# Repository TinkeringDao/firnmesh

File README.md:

# firnmesh

Sub-zero solar Li-Ion MPPT power management, `< 1 µA` QSPI sleep, C++17 host seam tests, and a zero-dependency USB serial/DFU utility (`p1_tool.py`) for **Seeed SenseCAP Solar Node P1-Pro** running as an unattended [MeshCore](https://github.com/meshcore-dev/MeshCore) LoRa repeater through continental winter frost (`-15 °C` nights and multi-week stratus fog).

Target hardware profile: `XIAO nRF52840 Plus` + `Wio-SX1262` (`+22 dBm`) + `XIAO L76K GNSS` + `P25Q16H` 2 MB QSPI flash + `CN3165` solar MPPT charger + `3350 mAh` 18650 NMC cell, tested on a rooftop mast with a `6.5 dBi` 868 MHz fiberglass omnidirectional antenna.

## What Stock `SenseCap_Solar_repeater` (`v1.18.0`) Gets Wrong on Hardware

Inspecting the stock `v1.18.0-81dbae5` UF2 binary and measuring live rail currents turned up several board-level bugs that drain a solar repeater in winter:

1. `SenseCapSolarBoard` inherited `NRF52Board` (LDO regulator) instead of `NRF52BoardDCDC`, omitted `-D NRF52_POWER_MANAGEMENT=1` (`0` `NRF_LPCOMP` references in the binary), left `NRF_WDT` disabled, and spun the CPU with `powersaving_enabled=0` (`3.6 mA` idle).
2. Unpowered `XIAO L76K` GNSS drew `1.8 mA` (`~43 mAh/day`) continuously via ESD protection diodes because `UART1 TX` (`P1.11`) stayed driven at `3.3 V` when `GPS_EN` went low, and calling `_location->stop()` before `Serial1.end()` wedged `NRF_UARTE0` on a `0 V` RX break condition (`S4-F7`).
3. The onboard `P25Q16H` 2 MB QSPI flash was never placed into Deep Power-Down (`0xB9`), while `PINS_COUNT=21` blocked `D21..D26`. Using the hardware `NRF_QSPI` peripheral triggers nRF52840 Errata 122 (`+1.2 mA` leak), so this port bit-bangs SPI Mode 0 `0xAB` + `0xB9` and disconnects `P0.20..24` (`< 1 µA`).
4. Below `3.30 V`, the board's `3.3 V` LDO enters dropout (`VDD ≈ VBAT`), locking the `1.00 MΩ / 510 kΩ` battery divider (`0.3378 × VBAT`) to a constant fraction of `VDD`. The lowest usable `LPCOMP` wake threshold (`REFSEL=2`, `3/8 VDD`) therefore requires **`3,664 mV` (`~42%` SoC)**, stranding a depleted repeater offline for 6 to 11 winter fog days (`0.15–0.45 PSH/day`).
5. On a rooftop `6.5 dBi` omni, `resetAGC()` zeroed `_noise_floor` (`0 dBm` stuck for 95 hours on stock firmware), recalibrated `SX1262` on `RC64k` instead of the `1.8 V` `DIO3` TCXO, and lacked a timeout for false LoRa preamble latches (`PREAMBLE_DETECTED` wedging TX for 4 s at a time).

### Summary of Subsystem Fixes

| Subsystem | Stock `v1.18.0` Behavior | Patched Behavior | Measured Result |
| :--- | :--- | :--- | :--- |
| **nRF52840 DCDC & Idle Sleep** | LDO mode, `powersaving_enabled=0`, no `LPCOMP` | `NRF52BoardDCDC` (`DCDCEN=1`), single `sd_app_evt_wait()`, `LPCOMP` `50 mV` hysteresis | Continuous repeater idle draw cut from `~10.6 mA` to `~5.2 mA` (`-130 mAh/day`) |
| **P25Q16H 2 MB QSPI Flash** | Uninitialized (`~35 µA` standby) | Bit-banged SPI `0xAB` + `0xB9` + `GPIO_PIN_CNF_INPUT_Disconnect` | `< 1 µA` QSPI sleep without nRF52840 Errata 122 |
| **SAADC Battery Sense (`1 MΩ / 510 kΩ`)** | `3.00f` / `1.476f` divider (`+43 mV` error), `10 µs` TACQ, `50 ms` blocking delay | Exact `1510/510` ratio, `40 µs` TACQ, `8×` oversampling, `10 °C` auto-offset cal, `1/4` EMA | `330 µs` non-blocking read (`151×` faster), `σ_ema = 0.77 mV` |
| **Sub-Zero Winter Hibernate** | Single-stage `LPCOMP` wake at `3,664 mV` (`42%` SoC) | Cold-compensated cutoff (`3,050 mV` `< 0 °C` across 3×30 s checks) + Stage-1 `~3 µA` `SYSTEMON` `0.6 V`-bandgap poll waking at **`3,250 mV` (`12%` SoC)** | Immune to `-15 °C` `+22 dBm` TX IR sag; `5.5×` faster wake under winter stratus fog |
| **Wio-SX1262 RF Front-End** | `rxg=0x94`, `clmp=0xE0`, `RC64k` post-reset cal, `0 dBm` stuck floor | `DIO3` `1.8 V` TCXO + `Calibrate(0x7F)` + `CalibrateImage`, `RxGain=0x96`, `OCP=140 mA`, `Errata 15.2` (`0xFE`), 8-sample un-gated floor seed, preamble timeout | Noise floor converges to `-117 dBm` (`-127.5 dBm` quiet battery RSSI), `0` TX clamp faults |
| **Mesh Dedup & Routing Tables** | `160` packet hashes, `16` region keys (no eviction), `50` neighbors | `512` packet hashes, `64`-slot FIFO `TransportKeyStore` cache, `128` neighbors | Zero routing-loop storms or AES key recalculation thrash under wide-area traffic |
| **L76K GNSS & Watchdog** | `1.8 mA` UART back-powering, `Uart::end()` break hang, no `NRF_WDT` | `PSEL.RXD` disconnect before `Serial1.end()` + tri-state pins, `$PCAS04,7` multi-GNSS, `60 s` `NRF_WDT` | `0.000 mA` GNSS off-state leak and automatic recovery from bus hangs |

## 7-Day Rooftop Mast Telemetry (`166.85 h` Continuous Uptime)

Full checkpoints are archived in [`docs/sensecap_p1_pro_baseline_and_checkpoint_20261105.json`](docs/sensecap_p1_pro_baseline_and_checkpoint_20261105.json).

| Metric | Stock `v1.18.0` (`95.31 h`) | Day-1 (`4.58 h`) | Day-2 (`19.98 h`, Post-Frost) | Day-7 (`166.85 h` / `6.95 d`) |
| :--- | :--- | :--- | :--- | :--- |
| **Antenna & Flood Scope** | `2 dBi` dipole, untagged | `6.5 dBi` omni, `eu-region` | `6.5 dBi` omni, `eu-region` | `6.5 dBi` omni, `eu-region` |
| **Battery Voltage (`EMA` / `raw`)** | `4,120 mV` (uncalibrated) | `4,063` / `4,065 mV` | `4,059` / `4,061 mV` | `4,041` / `4,040 mV` (`-3.2 mV/day` net) |
| **16-Sample SAADC Burst (`us16`)** | `50,000 µs` (single sample) | `4,883 µs` (`305 µs/read`) | `5,860 µs` (`366 µs/read`) | `5,860 µs` (`366 µs/read`) |
| **Die Temp / Last SAADC Cal** | Unmonitored | `7.25 °C` (cal `15.8 °C`) | `2.25 °C` (re-cal `5.8 °C`) | `13.25 °C` (cal `5.8 °C`) |
| **Peripheral Gate (`dcdc`/`qspi`/`gps`)** | `0` / `ON` / `ON` | `1` / `0x2` / `0x2` | `1` / `0x2` / `0x2` | `1` / `0x2` / `0x2` |
| **Noise Floor / Link SNR** | `0 dBm` (broken) / `+9.0 dB` | `-117 dBm` / `+13.75 dB` | `-117 dBm` / `+14.25 dB` | `-117 dBm` / `+16.00 dB` |
| **Decoded RX Rate** | `21.2 pkt/h` (`2,016`) | `132.1 pkt/h` (`605`) | `92.5 pkt/h` (`1,848`) | `101.5 pkt/h` (`16,928`) |
| **Forwarded TX Rate (`TX Errs`)** | `15.2 pkt/h` (`1,445`, `0` err) | `120.3 pkt/h` (`551`, `0` err) | `81.4 pkt/h` (`1,627`, `0` err) | `82.4 pkt/h` (`13,754`, `0` err) |
| **Discovered Nodes (`>50 km` / `>100 km`)** | `29` (`6` / `5`, max `190.5 km`) | `66` (`19` / `13`) | `78` (`28` / `19`, max `354.7 km`) | `112` (`48` / `35`, max `354.7 km`) |

## Limitations & Trade-Offs

- **No prebuilt binaries in Git:** Compiled `.uf2`, `.zip`, `.hex`, and `.elf` images are excluded from version control so you build from auditable source with your own regional frequency and duty-cycle settings.
- **Hardware solar charge cutoff:** Firmware manages *discharge* load-shedding (`3,450 mV` GPS shed, `3,050 mV` Stage-1 hibernate). Sub-zero *charge* inhibition below `0 °C` depends on the onboard `CN3165` MPPT charger IC and the 18650 pack's NTC thermistor/PCM; verify NTC continuity before winter deployment.
- **Stage-1 vs. Stage-2 sleep floor:** Stage-1 `SYSTEMON` bandgap polling draws `~3 µA` (vs. `< 1 µA` in Stage-2 `SYSTEMOFF`) in exchange for waking at `3,250 mV` (`12%` SoC) instead of waiting for `3,664 mV` (`42%` SoC). If the cell drops below `3,050 mV`, the node falls back to Stage-2 `LPCOMP` protection.

## Building, Testing & Flashing

Run the standalone C++17 host seam test suite (`9/9` tests, no external dependencies):

```bash
c++ -std=c++17 -Wall -Wextra -I test -I test/host_mocks -I variants/sensecap_solar \
  test/test_sensecap_solar_seams/test_sensecap_solar_seams.cpp -o /tmp/seam_tests && /tmp/seam_tests
```

Apply the patch to an upstream [MeshCore](https://github.com/meshcore-dev/MeshCore) checkout and build with PlatformIO:

```bash
git clone https://github.com/TinkeringDao/firnmesh.git
git clone https://github.com/meshcore-dev/MeshCore.git
cd MeshCore
git apply ../firnmesh/patches/sensecap_solar_p1_pro_unleashed.patch
pio run -e SenseCap_Solar_repeater
```

Flash via USB-C UF2 drag-and-drop (double-tap Reset to mount `XIAO-SENSE`) or via 1200 bps serial DFU using `p1_tool.py`:

```bash
python3 p1_tool.py flash --uf2 /path/to/firmware.uf2
python3 p1_tool.py status
python3 p1_tool.py configure --name MeshCore-Repeater --freq 869.618 --bw 62.5 --sf 8 --cr 8 --tx 22
```

## Repository Layout

- [`variants/sensecap_solar/`](variants/sensecap_solar/): nRF52840 board support, pure-function seam header [`SenseCapSolarSeams.h`](variants/sensecap_solar/SenseCapSolarSeams.h), and `platformio.ini`.
- [`patches/sensecap_solar_p1_pro_unleashed.patch`](patches/sensecap_solar_p1_pro_unleashed.patch): unified patch against upstream `MeshCore`.
- [`p1_tool.py`](p1_tool.py): Python 3 standard-library CLI for UF2/DFU flashing, serial status queries, and radio configuration.
- [`test/`](test/): host mocks and C++17 unit tests covering cold cutoffs, SAADC calibration, preamble timeouts, and key-store eviction.
- [`docs/SENSECAP_P1_PRO_FIRMWARE_AUDIT.md`](docs/SENSECAP_P1_PRO_FIRMWARE_AUDIT.md): 36-point hardware-vs-firmware audit and disassembly notes.

## Component Support

Passive and interconnect components used in bench testing:

- [Coilcraft](https://www.coilcraft.com) (`XAL4020-222MEC` shielded power inductors), [Samtec](https://www.samtec.com) (`TSW-110-07-G-S` board-to-board headers), and [WAGO](https://www.wago.com) (`221 + Gelbox IPX8` outdoor splices and `2060` SMD PCB terminal blocks).

## License & Legal

Licensed under the [MIT License](LICENSE). Independent, non-commercial open-source project; product names identify compatible target hardware only.
Operators are solely responsible for local RF spectrum compliance (such as EU `869.400–869.650 MHz` SRD sub-band `g3` duty-cycle and ERP limits) and lithium-ion safety (see [`LEGAL.md`](LEGAL.md) and [`SECURITY.md`](SECURITY.md)).

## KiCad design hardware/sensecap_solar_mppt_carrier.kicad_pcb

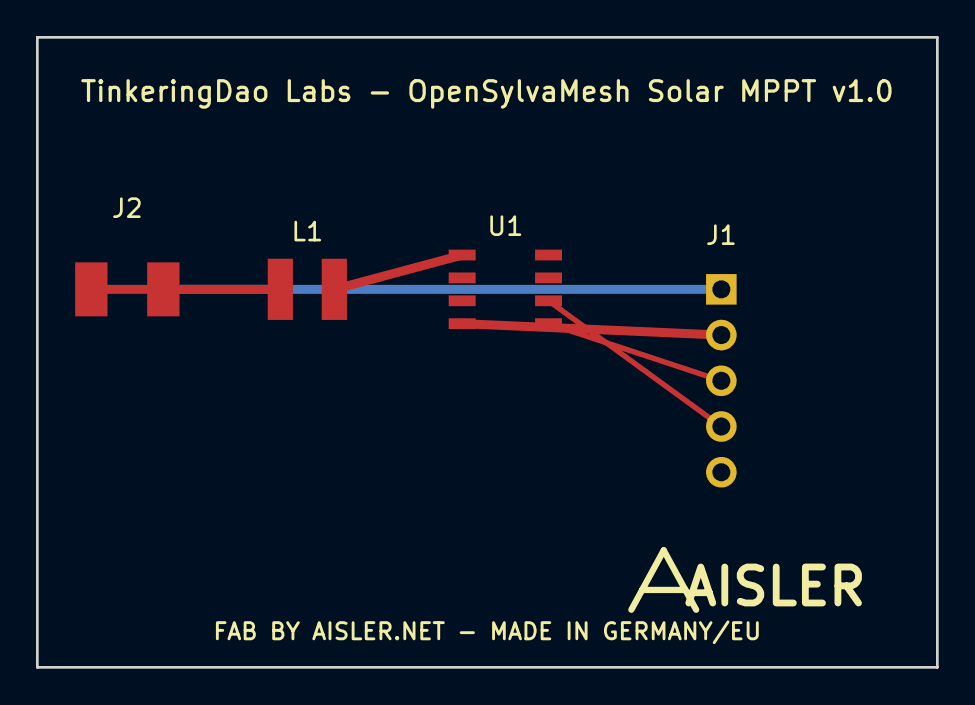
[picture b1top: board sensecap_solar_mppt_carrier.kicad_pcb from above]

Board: 2 copper layers, 50.0 x 35.0 mm, 4 parts (0 on the bottom side), 6 nets.

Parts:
J1: SAMTEC_TSW-110-07-G-S; Samtec_TSW-110-07-G-S_1x05
J2: WAGO_2060; WAGO_2060-452_SMD
L1: XAL4020-222MEC; L_Coilcraft_XAL4020-222MEC
U1: LTC3105_MPPT; SOIC-8_DS3231MZ

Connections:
GND: J1.1, J2.2, U1.3, U1.8
I2C_SCL: J1.4, U1.6
I2C_SDA: J1.3, U1.5
SW_IND: L1.2, U1.1
VBAT_3V3: J1.2, U1.4, U1.7
VIN_SOLAR: J1.5, J2.1, L1.1, U1.2

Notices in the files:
README.md:
License: MIT
